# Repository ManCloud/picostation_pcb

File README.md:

# picostation_pcb

This is my adaption of the PicoStation PCB for [paulocode](https://github.com/paulocode)s [PicoStation](https://github.com/paulocode/picostation).  
This layout was made to be completely purchaseable by JLCPCB therefore all partsnumbers etc. are included in the Project.

---

## NOTICE ##
for this board to properly work the crystal-wait time needs to be extended.  

For this you need to add the follwing lines in CmakeLists.txt under "add_executable(picostation)" :

>target_compile_definitions(  
>picostation PUBLIC  
>PICO_XOSC_STARTUP_DELAY_MULTIPLIER=64  
>) 

---

 - The FFC cable is the same one that comes with an Xstation

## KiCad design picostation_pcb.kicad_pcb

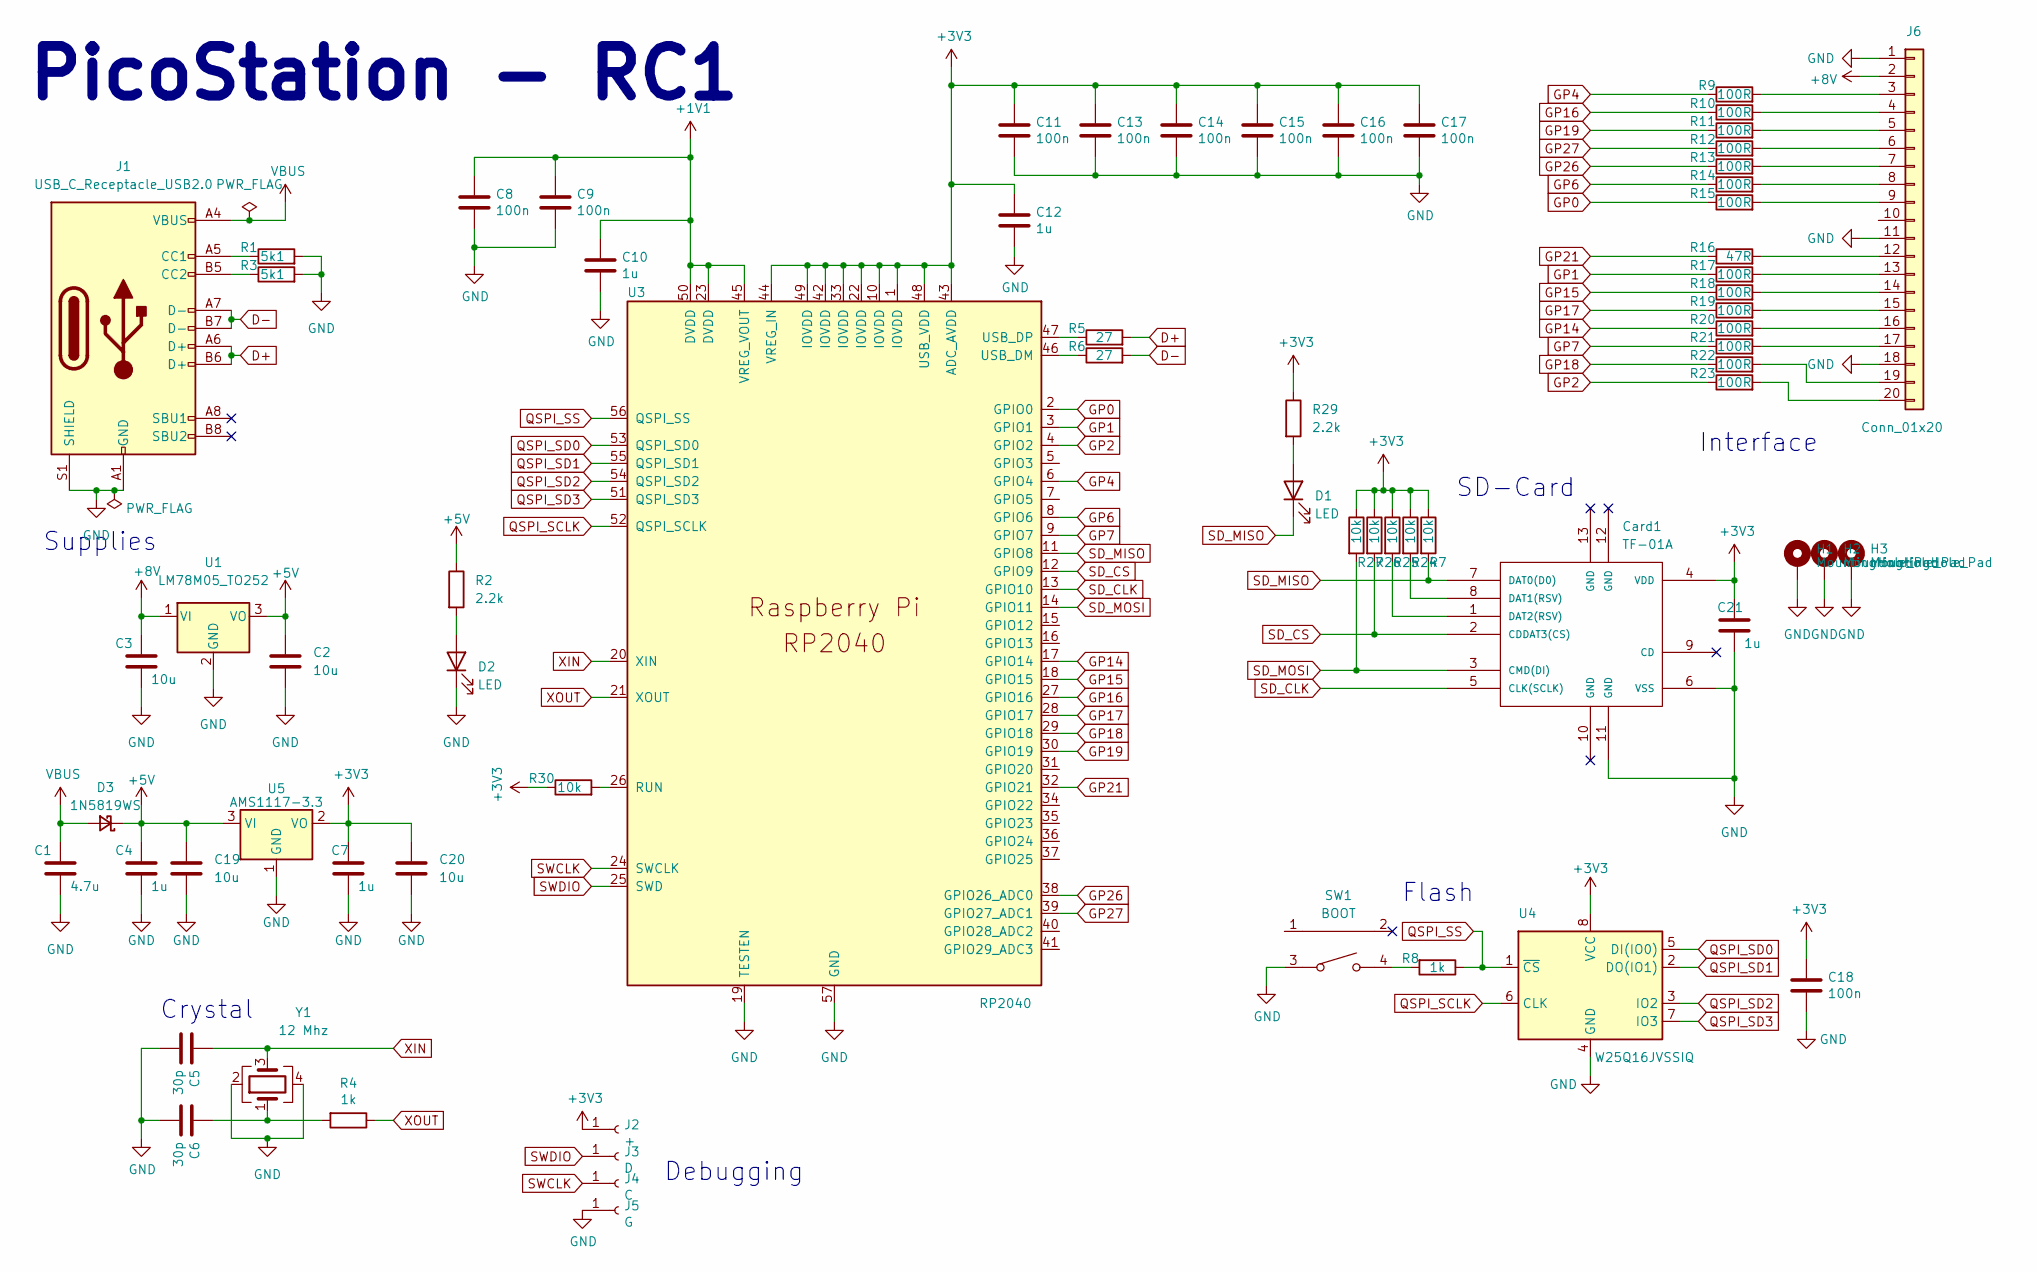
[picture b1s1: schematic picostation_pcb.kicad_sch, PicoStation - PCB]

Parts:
C1: 4.7u; C_0603_1608Metric_Pad1.08x0.95mm_HandSolder; LCSC C23733
C2, C3, C19, C20: 10u; C_0805_2012Metric_Pad1.18x1.45mm_HandSolder; LCSC C15850
C4, C7, C10, C12, C21: 1u; C_0603_1608Metric_Pad1.08x0.95mm_HandSolder; LCSC C52923
C5, C6: 30p; C_0603_1608Metric_Pad1.08x0.95mm_HandSolder; LCSC C1570
C8, C9, C11, C13, C14, C15, C16, C17, C18: 100n; C_0603_1608Metric_Pad1.08x0.95mm_HandSolder; LCSC C1525
Card1: TF-01A; TF-SMD_TF-01A; LCSC C91145
D1, D2: LED; LED_0805_2012Metric_Pad1.15x1.40mm_HandSolder
D3: 1N5819WS; D_SOD-323; LCSC C191023
H1, H2, H3: MountingHole_Pad; MountingHole_2.2mm_M2_DIN965_Pad
J1: USB_C_Receptacle_USB2.0; USB_C_Receptacle_HRO_TYPE-C-31-M-12; LCSC C2765186
J2: +; TestPoint_Pad_D1.5mm
J3: D; TestPoint_Pad_D1.5mm
J4: C; TestPoint_Pad_D1.5mm
J5: G; TestPoint_Pad_D1.5mm
J6: Conn_01x20; Molex_200528-0200_1x20-1MP_P1.00mm_Horizontal
R1, R3: 5k1; R_0603_1608Metric_Pad0.98x0.95mm_HandSolder
R2, R29: 2.2k; R_0603_1608Metric_Pad0.98x0.95mm_HandSolder
R4, R8: 1k; R_0603_1608Metric_Pad0.98x0.95mm_HandSolder; LCSC C11702
R5, R6: 27; R_0603_1608Metric_Pad0.98x0.95mm_HandSolder
R7, R24, R25, R26, R27, R30: 10k; R_0603_1608Metric_Pad0.98x0.95mm_HandSolder
R9, R10, R11, R12, R13, R14, R15, R17, R18, R19, R20, R21, R22, R23: 100R; R_0603_1608Metric_Pad0.98x0.95mm_HandSolder
R16: 47R; R_0603_1608Metric_Pad0.98x0.95mm_HandSolder
SW1: BOOT; SW-SMD_TS24CA; LCSC C393942
U1: LM78M05_TO252; TO-252-2
U3: RP2040; RP2040-QFN-56; LCSC C2040
U4: W25Q16JVSSIQ; SOIC-8_5.23x5.23mm_P1.27mm; LCSC C131025
U5: AMS1117-3.3; SOT-223-3_TabPin2; LCSC C6186
Y1: 12 Mhz; Crystal_SMD_3225-4Pin_3.2x2.5mm; LCSC C9002

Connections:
+1V1: C8.1, C9.1, C10.1, U3.23 (DVDD), U3.45 (VREG_VOUT), U3.50 (DVDD)
+3V3: C7.1, C11.1, C12.1, C13.1, C14.1, C15.1, C16.1, C17.1, C18.1, C20.1, C21.1, Card1.4 (VDD), J2.1, R7.1, R24.1, R25.1, R26.1, R27.1, R29.1, R30.1, U3.1 (IOVDD), U3.10 (IOVDD), U3.22 (IOVDD), U3.33 (IOVDD), U3.42 (IOVDD), U3.43 (ADC_AVDD), U3.44 (VREG_IN), U3.48 (USB_VDD), U3.49 (IOVDD), U4.8 (VCC), U5.2 (VO); also elsewhere on the board
+5V: C2.1, C4.1, C19.1, D3.1 (K), R2.1, U1.3 (VO), U5.3 (VI)
+8V: C3.1, J6.2, U1.1 (VI)
D+: J1.A6 (D+), J1.B6 (D+), R5.2
D-: J1.A7 (D-), J1.B7 (D-), R6.2
GND: C1.1, C2.2, C3.2, C4.2, C5.2, C6.2, C7.2, C8.2, C9.2, C10.2, C11.2, C12.2, C13.2, C14.2, C15.2, C16.2, C17.2, C18.2, C19.2, C20.2, C21.2, Card1.6 (VSS), Card1.11 (GND), D2.1 (K), H1.1, H2.1, H3.1, J1.A1 (GND), J1.A12 (GND), J1.B1 (GND), J1.B12 (GND), J1.S1 (SHIELD), J5.1, J6.1, J6.11, J6.18, R1.2, R3.2, SW1.3, U1.2 (GND), U3.19 (TESTEN), U3.57 (GND), U4.4 (GND), U5.1 (GND), Y1.2, Y1.4
GP0: R15.1, U3.2 (GPIO0)
GP1: R17.1, U3.3 (GPIO1)
GP2: R23.1, U3.4 (GPIO2)
GP4: R9.1, U3.6 (GPIO4)
GP6: R14.1, U3.8 (GPIO6)
GP7: R21.1, U3.9 (GPIO7)
GP14: R20.1, U3.17 (GPIO14)
GP15: R18.1, U3.18 (GPIO15)
GP16: R10.1, U3.27 (GPIO16)
GP17: R19.1, U3.28 (GPIO17)
GP18: R22.1, U3.29 (GPIO18)
GP19: R11.1, U3.30 (GPIO19)
GP21: R16.1, U3.32 (GPIO21)
GP26: R13.1, U3.38 (GPIO26_ADC0)
GP27: R12.1, U3.39 (GPIO27_ADC1)
unnamed: C6.1, R4.2, Y1.1
unnamed: Card1.8 (DAT1(RSV)), R24.2
unnamed: Card1.1 (DAT2(RSV)), R25.2
unnamed: D1.2 (A), R29.2
unnamed: D2.2 (A), R2.2
unnamed: J1.A5 (CC1), R1.1
unnamed: J1.B5 (CC2), R3.1
unnamed: J6.3, R9.2
unnamed: J6.4, R10.2
unnamed: J6.5, R11.2
unnamed: J6.6, R12.2
unnamed: J6.7, R13.2
unnamed: J6.8, R14.2
unnamed: J6.9, R15.2
unnamed: J6.12, R16.2
unnamed: J6.13, R17.2
unnamed: J6.14, R18.2
unnamed: J6.15, R19.2
unnamed: J6.16, R20.2
unnamed: J6.17, R21.2
unnamed: J6.19, R22.2
unnamed: J6.20, R23.2
unnamed: R8.2, SW1.4
unnamed: R30.2, U3.26 (RUN)
unnamed: R6.1, U3.46 (USB_DM)
unnamed: R5.1, U3.47 (USB_DP)
QSPI_SCLK: U3.52 (QSPI_SCLK), U4.6 (CLK)
QSPI_SD0: U3.53 (QSPI_SD0), U4.5 (DI(IO0))
QSPI_SD1: U3.55 (QSPI_SD1), U4.2 (DO(IO1))
QSPI_SD2: U3.54 (QSPI_SD2), U4.3 (IO2)
QSPI_SD3: U3.51 (QSPI_SD3), U4.7 (IO3)
QSPI_SS: R8.1, U3.56 (QSPI_SS), U4.1 (~CS)
SD_CLK: Card1.5 (CLK(SCLK)), U3.13 (GPIO10); also elsewhere on the board
SD_CS: Card1.2 (CDDAT3(CS)), R26.2, U3.12 (GPIO9)
SD_MISO: Card1.7 (DAT0(D0)), D1.1 (K), R7.2, U3.11 (GPIO8)
SD_MOSI: Card1.3 (CMD(DI)), R27.2, U3.14 (GPIO11)
SWCLK: J4.1, U3.24 (SWCLK)
SWDIO: J3.1, U3.25 (SWD)
VBUS: C1.2, D3.2 (A), J1.A4 (VBUS), J1.A9 (VBUS), J1.B4 (VBUS), J1.B9 (VBUS)
XIN: C5.1, U3.20 (XIN), Y1.3
XOUT: R4.1, U3.21 (XOUT)

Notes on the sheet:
SD-Card
Flash
Debugging
Interface
Crystal
Supplies
PicoStation - RC1

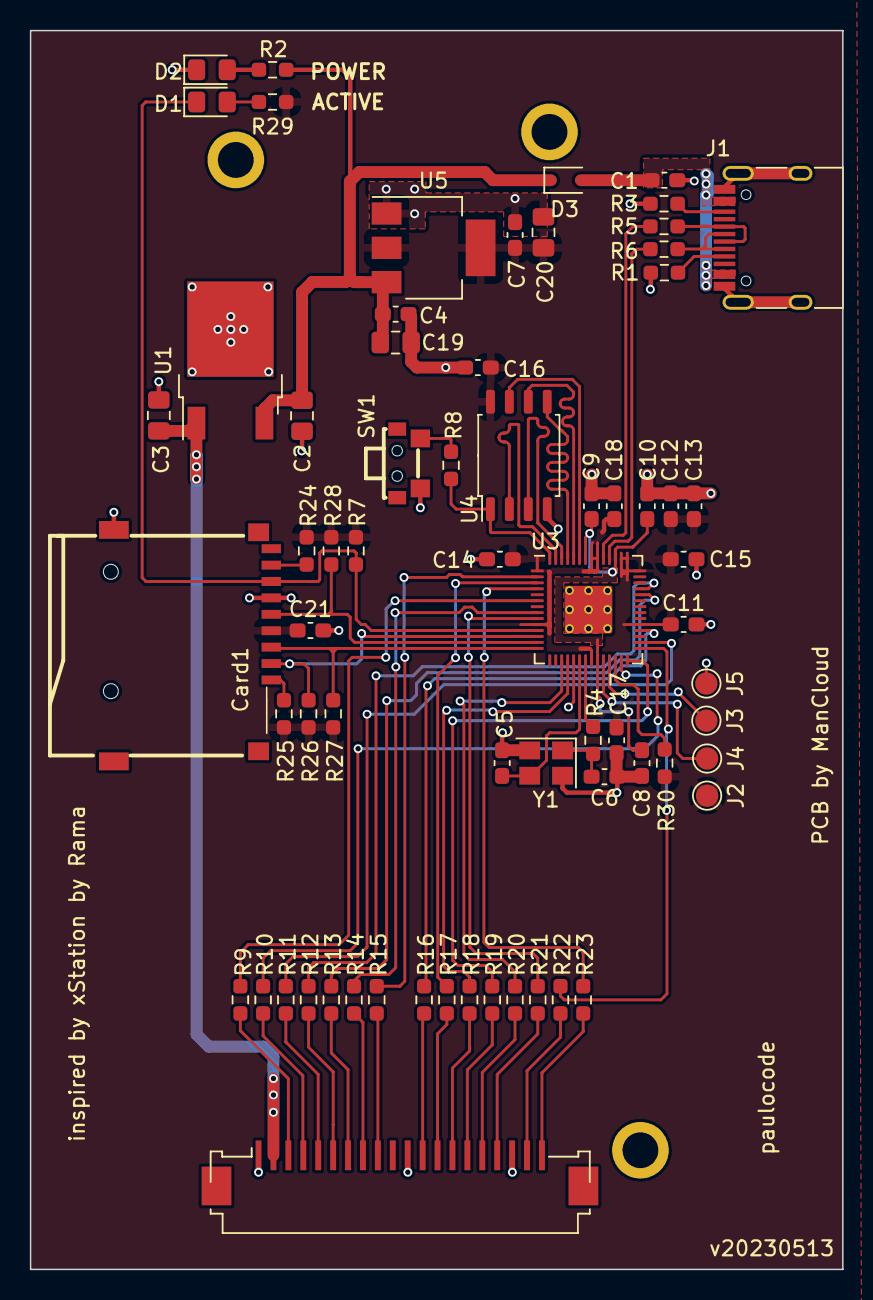
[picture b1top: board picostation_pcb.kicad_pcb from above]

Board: 2 copper layers, 54.5 x 83.1 mm, 70 parts (0 on the bottom side), 63 nets.

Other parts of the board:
R28: 10k; R_0603_1608Metric_Pad0.98x0.95mm_HandSolder

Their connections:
+3V3: R28.1; also elsewhere on the board
SD_CLK: R28.2; also elsewhere on the board

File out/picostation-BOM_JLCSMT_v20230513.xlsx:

Comment | Designator | Footprint | JLCPCB Part #（optional）
2.2k | R29,R2 | R_0603_1608Metric_Pad0.98x0.95mm_HandSolder | C4190
LED | D1,D2 | LED_0805_2012Metric_Pad1.15x1.40mm_HandSolder | C84256
10k | R28,R24,R7,R27,R26,R25,R30 | R_0603_1608Metric_Pad0.98x0.95mm_HandSolder | C25804
100n | C16,C8,C9,C17,C13,C18,C15,C14,C11 | C_0603_1608Metric_Pad1.08x0.95mm_HandSolder | C14663
100R | R12,R23,R18,R13,R10,R9,R20,R14,R21,R11,R15,R22,R17,R19 | R_0603_1608Metric_Pad0.98x0.95mm_HandSolder | C22775
47R | R16 | R_0603_1608Metric_Pad0.98x0.95mm_HandSolder | C23182
1u | C4,C21,C10,C12,C7 | C_0603_1608Metric_Pad1.08x0.95mm_HandSolder | C15849
10u | C19,C2,C3,C20 | C_0805_2012Metric_Pad1.18x1.45mm_HandSolder | C15850
1k | R8,R4 | R_0603_1608Metric_Pad0.98x0.95mm_HandSolder | C21190
5k1 | R3,R1 | R_0603_1608Metric_Pad0.98x0.95mm_HandSolder | C23186
AMS1117-3.3 | U5 | SOT-223-3_TabPin2 | C6186
Conn_01x20 | J6 | Molex_200528-0200_1x20-1MP_P1.00mm_Horizontal | C2914079
12 Mhz | Y1 | Crystal_SMD_3225-4Pin_3.2x2.5mm | C9002
USB_C_Receptacle_USB2.0 | J1 | USB_C_Receptacle_HRO_TYPE-C-31-M-12 | C2765186
LM78M05_TO252 | U1 | TO-252-2 | C58069
W25Q16JVSSIQ | U4 | SOIC-8_5.23x5.23mm_P1.27mm | C131025
BOOT | SW1 | SW-SMD_TS24CA | C393942
4.7u | C1 | C_0603_1608Metric_Pad1.08x0.95mm_HandSolder | C19666
27 | R5,R6 | R_0603_1608Metric_Pad0.98x0.95mm_HandSolder | C25190
30p | C5,C6 | C_0603_1608Metric_Pad1.08x0.95mm_HandSolder | C1658
TF-01A | Card1 | TF-SMD_TF-01A | C91145
1N5819WS | D3 | D_SOD-323 | C191023
RP2040 | U3 | RP2040-QFN-56 | C2040

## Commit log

2023-05-02 updated PCB
2023-05-02 added PDF-Files
2023-05-02 updated images
2023-05-02 fixed typo
2023-05-02 removed unecessary files
2023-05-13 Updated Board
    * removed SD-Cart Clock PullUp
    * added Active-LED (untested)
    * added Run PullUp
2023-05-13 added production files
